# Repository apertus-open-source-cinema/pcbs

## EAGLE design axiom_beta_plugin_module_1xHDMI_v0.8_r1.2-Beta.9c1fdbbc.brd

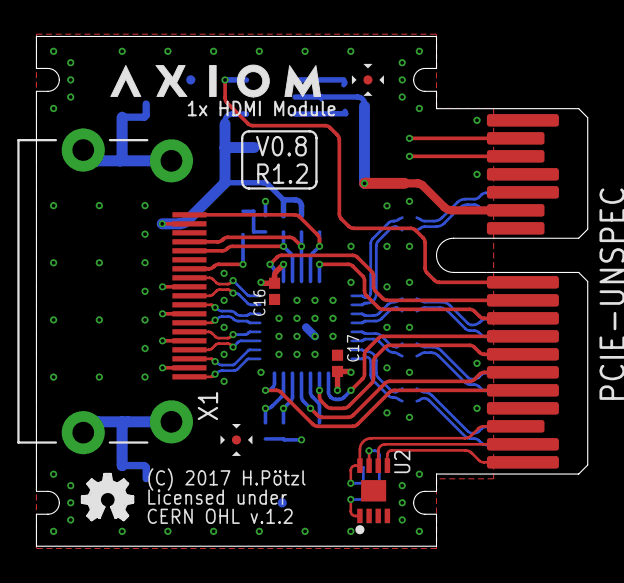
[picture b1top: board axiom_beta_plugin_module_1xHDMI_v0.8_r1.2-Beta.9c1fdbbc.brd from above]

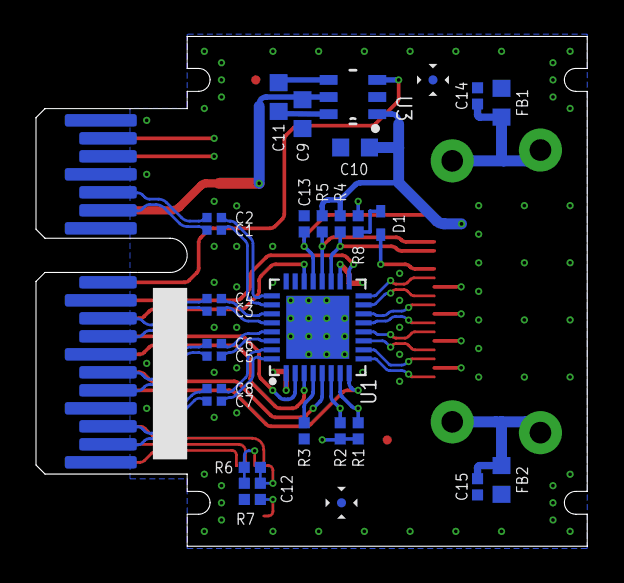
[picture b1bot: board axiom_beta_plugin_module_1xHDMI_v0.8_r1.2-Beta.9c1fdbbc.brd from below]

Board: 4 copper layers, 30.6 x 28.3 mm, 39 parts (30 on the bottom side), 50 nets.

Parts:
C1, C2, C3, C4, C5, C6, C7, C8: 100n; 0402-C
C9: 2u2; 0603-B
C10: 10u; 0603-B
C11: 220n; 0603-B
C12, C16, C17: 100n; 0402-B
C13: 1-10n; 0402-B
C14, C15: 10n; 0402-B
D1: SOD523
F1, F2, F3, F4: FIDUCIAL; FID_ARROW
FB1, FB2: 0603-B
LOGO2: OSHW_LOGO_FILLX0100-NT; OSHW_FILLX100_NOTEXT
PCIE-UNSPEC: PCIE-36-AXIOM
R1, R2, R4, R5: 2k2; 0402-B
R3: 12k4; 0402-B
R6: 10k; 0402-B
R7: 1k; 0402-B
R8: 0402-B
U1: PTN3363; HVQFN32
U2: BR24G04NUX; DFN200X300X100-9N
U3: REG710-DBV; DBV
U$1: AXIOM_LOGO459X70; AXIOM_LOGO_459X70
X1: HDMI-10029449; 10029449-X01XLF

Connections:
3V3: C9.1, C16.1, C17.1, PCIE-UNSPEC.B13, R1.1, R2.1, R8.1, U1.1, U1.18, U3.5
5V0: C10.1, R4.1, R5.1, U3.1, X1.18
!OE!: PCIE-UNSPEC.B10, U1.17
CLOCK_N: U1.16, X1.12
CLOCK_P: U1.15, X1.10
DATA0_N: U1.14, X1.9
DATA0_P: U1.13, X1.7
DATA1_N: U1.12, X1.6
DATA1_P: U1.11, X1.4
DATA2_N: U1.10, X1.3
DATA2_P: U1.9, X1.1
DDC_EN: PCIE-UNSPEC.B9, U1.22
DDET: PCIE-UNSPEC.B7, U1.3
EN: PCIE-UNSPEC.B11, U3.3
EQ0: PCIE-UNSPEC.B5, U1.8
EQ1: PCIE-UNSPEC.B8, U1.2
GND: C9.2, C10.2, C12.2, C13.2, C14.2, C15.2, C16.2, C17.2, FB1.2, FB2.2, PCIE-UNSPEC.A1, PCIE-UNSPEC.A4, PCIE-UNSPEC.A7, PCIE-UNSPEC.A10, PCIE-UNSPEC.A12, PCIE-UNSPEC.A15, PCIE-UNSPEC.A18, PCIE-UNSPEC.B15, PCIE-UNSPEC.B18, R3.2, R7.2, U1.24, U1.EP, U2.1, U2.2, U2.3, U2.4, U2.EP, U3.2, X1.2, X1.5, X1.8, X1.11, X1.17
HDMI_CEC: D1.C, X1.13
HDMI_HP: C13.1, U1.21, X1.19
HDMI_SCL: R4.2, U1.19, X1.15
HDMI_SDA: R5.2, U1.20, X1.16
I2C_V: C12.1, PCIE-UNSPEC.B3, R6.1, U2.8
IHP: PCIE-UNSPEC.B6, U1.5
IN_D1_N: C2.1, U1.25
IN_D1_P: C1.1, U1.26
IN_D2_N: C4.1, U1.27
IN_D2_P: C3.1, U1.28
IN_D3_N: C6.1, U1.29
IN_D3_P: C5.1, U1.30
IN_D4_N: C8.1, U1.31
IN_D4_P: C7.1, U1.32
ISCL: PCIE-UNSPEC.B16, R1.2, U1.7
ISDA: PCIE-UNSPEC.B17, R2.2, U1.6
LVDS_0_N: C8.2, PCIE-UNSPEC.A3
LVDS_0_P: C7.2, PCIE-UNSPEC.A2
LVDS_1_N: C6.2, PCIE-UNSPEC.A6
LVDS_1_P: C5.2, PCIE-UNSPEC.A5
LVDS_2_N: C4.2, PCIE-UNSPEC.A9
LVDS_2_P: C3.2, PCIE-UNSPEC.A8
LVDS_3_N: C2.2, PCIE-UNSPEC.A14
LVDS_3_P: C1.2, PCIE-UNSPEC.A13
unnamed: C11.1, U3.6
unnamed: C11.2, U3.4
unnamed: C14.1, FB1.1, X1.Z1, X1.Z2
unnamed: R6.2, R7.1, U2.7
unnamed: C15.1, FB2.1, X1.Z3, X1.Z4
unnamed: R3.1, U1.4
unnamed: D1.A, R8.2
SCL: PCIE-UNSPEC.B2, U2.6
SDA: PCIE-UNSPEC.B1, U2.5

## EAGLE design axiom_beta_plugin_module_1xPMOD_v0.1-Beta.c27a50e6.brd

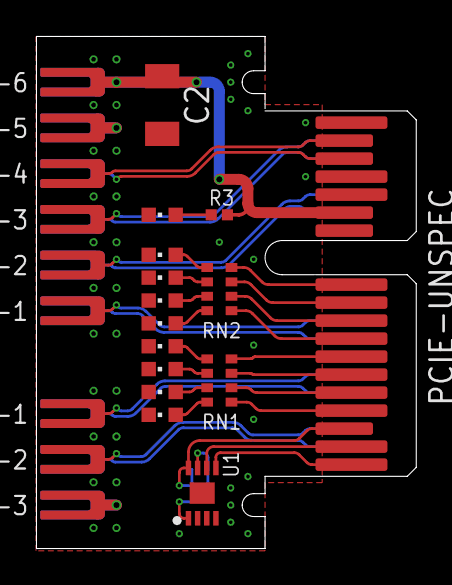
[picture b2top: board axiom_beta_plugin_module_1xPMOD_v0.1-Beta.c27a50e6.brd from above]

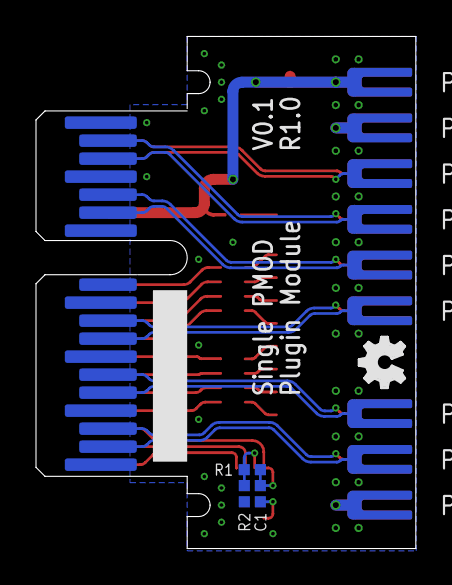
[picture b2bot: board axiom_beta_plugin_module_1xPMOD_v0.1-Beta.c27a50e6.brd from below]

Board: 4 copper layers, 21.1 x 28.4 mm, 38 parts (13 on the bottom side), 35 nets.

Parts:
C1: 100n; 0402-B
C2: 100u; 1206-A
LED0, LED1, LED2, LED3, LED4, LED5, LED6, LED7, LED8: CHIPLED_0603
LOGO1, LOGO2: OSHW_LOGO_FILLX0100-NT; OSHW_FILLX100_NOTEXT
PCIE-UNSPEC: PCIE-36-AXIOM
PMOD1-1, PMOD1-2, PMOD1-3, PMOD1-4, PMOD1-5, PMOD1-6, PMOD1-7, PMOD1-8, PMOD1-9, PMOD1-10, PMOD1-11, PMOD1-12, PMOD2-1, PMOD2-2, PMOD2-3, PMOD2-4, PMOD2-5, PMOD2-6: 1.6X3.8U-MM
R1, R3: 10k; 0402-B
R2: 1k; 0402-B
RN1, RN2: 10k; CAY16
U1: BR24G04NUX; DFN200X300X100-9N

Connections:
GND: C1.2, C2.2, LED0.C, LED1.C, LED2.C, LED3.C, LED4.C, LED5.C, LED6.C, LED7.C, LED8.C, PCIE-UNSPEC.A1, PCIE-UNSPEC.A4, PCIE-UNSPEC.A7, PCIE-UNSPEC.A10, PCIE-UNSPEC.A12, PCIE-UNSPEC.A15, PCIE-UNSPEC.A18, PCIE-UNSPEC.B15, PCIE-UNSPEC.B18, PMOD1-5.1, PMOD1-11.1, PMOD2-3.1, PMOD2-6.1, R2.2, U1.1, U1.2, U1.3, U1.4, U1.EP
I2C_V: C1.1, PCIE-UNSPEC.B3, R1.1, U1.8
IO0: PCIE-UNSPEC.B4, RN1.5
IO1: PCIE-UNSPEC.B5, RN1.6
IO2: PCIE-UNSPEC.B6, RN1.7
IO3: PCIE-UNSPEC.B7, RN1.8
IO4: PCIE-UNSPEC.B8, RN2.5
IO5: PCIE-UNSPEC.B9, RN2.6
IO6: PCIE-UNSPEC.B10, RN2.7
IO7: PCIE-UNSPEC.B11, RN2.8
LVDS_0_N: PCIE-UNSPEC.A3, PMOD2-2.1
LVDS_0_P: PCIE-UNSPEC.A2, PMOD2-5.1
LVDS_1_N: PCIE-UNSPEC.A6, PMOD2-1.1
LVDS_1_P: PCIE-UNSPEC.A5, PMOD2-4.1
LVDS_2_N: PCIE-UNSPEC.A9, PMOD1-1.1
LVDS_2_P: PCIE-UNSPEC.A8, PMOD1-7.1
LVDS_3_N: PCIE-UNSPEC.A14, PMOD1-2.1
LVDS_3_P: PCIE-UNSPEC.A13, PMOD1-8.1
LVDS_4_N: PCIE-UNSPEC.A17, PMOD1-3.1
LVDS_4_P: PCIE-UNSPEC.A16, PMOD1-9.1
LVDS_5_N: PCIE-UNSPEC.B17, PMOD1-4.1
LVDS_5_P: PCIE-UNSPEC.B16, PMOD1-10.1
unnamed: R1.2, R2.1, U1.7
unnamed: LED3.A, RN1.1
unnamed: LED2.A, RN1.2
unnamed: LED1.A, RN1.3
unnamed: LED0.A, RN1.4
unnamed: LED8.A, R3.2
unnamed: LED7.A, RN2.1
unnamed: LED6.A, RN2.2
unnamed: LED5.A, RN2.3
unnamed: LED4.A, RN2.4
PCIE_VCC: C2.1, PCIE-UNSPEC.B13, PMOD1-6.1, PMOD1-12.1, R3.1
SCL: PCIE-UNSPEC.B2, U1.6
SDA: PCIE-UNSPEC.B1, U1.5

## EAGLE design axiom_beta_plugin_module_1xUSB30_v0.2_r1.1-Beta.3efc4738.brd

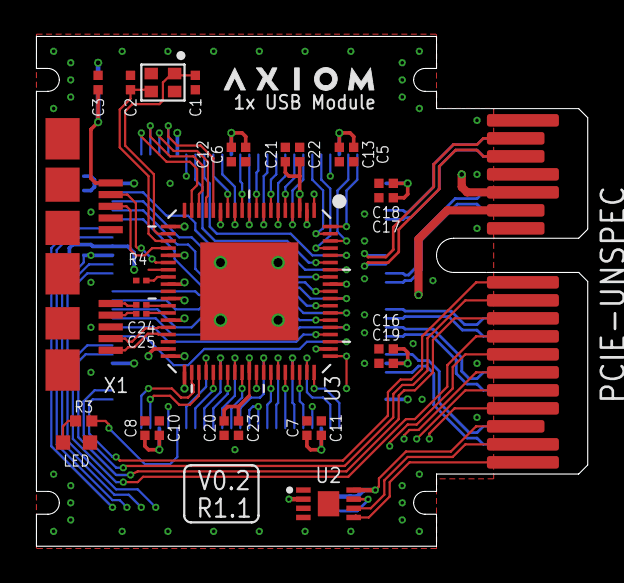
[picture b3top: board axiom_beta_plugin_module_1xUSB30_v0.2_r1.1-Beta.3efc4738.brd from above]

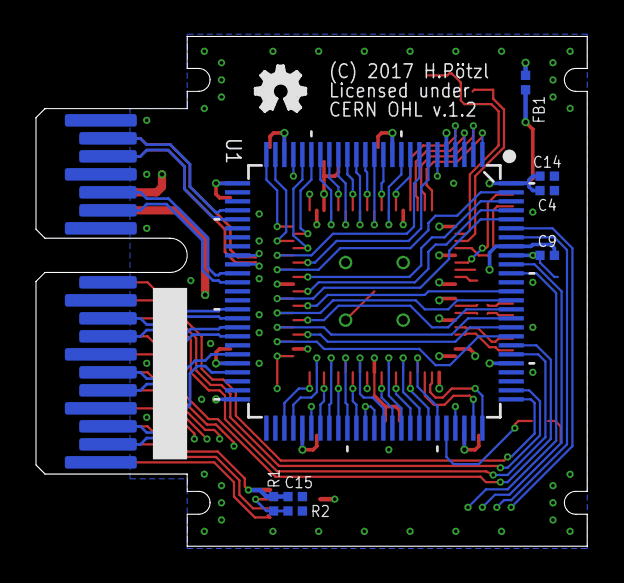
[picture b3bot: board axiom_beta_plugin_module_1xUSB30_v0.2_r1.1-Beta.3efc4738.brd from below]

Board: 4 copper layers, 30.6 x 28.3 mm, 39 parts (9 on the bottom side), 90 nets.

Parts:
C1, C2: 12p; 0402-C
C3, C9, C10, C11, C12, C13, C14, C15, C18, C19, C22, C23: 100n; 0402-C
C4, C5, C6, C7, C8, C16, C17, C20, C21: 4u7; 0402-C
C24, C25: 100n; 0201-C
FB1: 0402-C
LED: LED; CHIPLED_0603
LOGO2: OSHW_LOGO_FILLX0100-NT; OSHW_FILLX100_NOTEXT
PCIE-UNSPEC: PCIE-36-AXIOM
R1: 10k; 0402-C
R2: 1k; 0402-C
R3: 10k; 0402-B
R4: 1k6; 0201-C
U1: MACHXO2-100; MACHXO2-100TQFP
U2: BR24G04NUX; DFN200X300X100-9N
U3: FT601QQFN76; QFN76
U$: AXIOM_LOGO328X50; AXIOM_LOGO_328X50
X1: 10_USB_3.0_2S-SMT; MICRO-B-30-H-SMT
Y1: SMD-4P-2G-2.0X1.6; 2.0X1.6

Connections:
1V0: C20.1, C21.1, C22.1, C23.1, U3.2, U3.3, U3.30, U3.33, U3.39, U3.48
2V5: C16.1, C17.1, C18.1, C19.1, PCIE-UNSPEC.B14, U1.26, U1.46
3V3: C4.1, C5.1, C6.1, C7.1, C8.1, C9.1, C10.1, C11.1, C12.1, C13.1, C14.1, PCIE-UNSPEC.B13, U1.5, U1.11, U1.23, U1.50, U1.55, U1.73, U1.80, U1.93, U1.100, U3.14, U3.20, U3.24, U3.28, U3.38, U3.49, U3.59, U3.68
!OE: U1.9, U3.13
!RD: U1.10, U3.12
!RESET: U1.4, U3.15
!RXF: U1.14, U3.9
!SIWU: U1.13, U3.10
!TXE: U1.15, U3.8
!WAKEUP: U1.3, U3.16
!WR: U1.12, U3.11
BE_0: U1.19, U3.4
BE_1: U1.18, U3.5
BE_2: U1.17, U3.6
BE_3: U1.16, U3.7
CLK: U1.62, U1.63, U3.58
D0: U1.75, U3.40
D1: U1.74, U3.41
D2: U1.70, U3.42
D3: U1.69, U3.43
D4: U1.68, U3.44
D5: U1.67, U3.45
D6: U1.66, U3.46
D7: U1.65, U3.47
D8: U1.64, U3.50
D9: U1.61, U3.51
D10: U1.60, U3.52
D11: U1.59, U3.53
D12: U1.58, U3.54
D13: U1.57, U3.55
D14: U1.54, U3.56
D15: U1.53, U3.57
D16: U1.83, U3.60
D17: U1.84, U3.61
D18: U1.85, U3.62
D19: U1.86, U3.63
D20: U1.87, U3.64
D21: U1.88, U3.65
D22: U1.96, U3.66
D23: U1.97, U3.67
D24: U1.98, U3.69
D25: U1.99, U3.70
D26: U1.7, U3.71
D27: U1.8, U3.72
D28: U1.21, U3.73
D29: U1.24, U3.74
D30: U1.20, U3.75
D31: U1.25, U3.76
DM: U3.25, X1.2
DONE: PCIE-UNSPEC.B11, U1.76
DP: U3.23, X1.3
GND: C1.2, C2.2, C3.2, C4.2, C5.2, C6.2, C7.2, C8.2, C9.2, C10.2, C11.2, C12.2, C13.2, C14.2, C15.2, C16.2, C17.2, C18.2, C19.2, C20.2, C21.2, C22.2, C23.2, LED.C, PCIE-UNSPEC.A1, PCIE-UNSPEC.A4, PCIE-UNSPEC.A7, PCIE-UNSPEC.A10, PCIE-UNSPEC.A12, PCIE-UNSPEC.A15, PCIE-UNSPEC.A18, PCIE-UNSPEC.B15, PCIE-UNSPEC.B18, R2.2, R4.2, U1.6, U1.22, U1.33, U1.44, U1.49, U1.56, U1.72, U1.79, U1.89, U1.92, U2.1, U2.2, U2.3, U2.4, U2.EP, U3.1, U3.26, U3.29, U3.36, U3.77, X1.5, X1.8, X1.S1, X1.S2, X1.Z1, X1.Z2, X1.Z3, X1.Z4, Y1.2, Y1.4
GPIO0: U1.2, U3.17
GPIO1: U1.1, U3.18
I2C_V: C15.1, PCIE-UNSPEC.B3, R1.1, U2.8
INITN: PCIE-UNSPEC.B10, U1.77
JTAGENB: PCIE-UNSPEC.B8, U1.82
LED: R3.1, U1.71
LVDS_0_N: PCIE-UNSPEC.A3, U1.45
LVDS_0_P: PCIE-UNSPEC.A2, U1.47
LVDS_1_N: PCIE-UNSPEC.A6, U1.42
LVDS_1_P: PCIE-UNSPEC.A5, U1.43
LVDS_2_N: PCIE-UNSPEC.A9, U1.40
LVDS_2_P: PCIE-UNSPEC.A8, U1.41
LVDS_3_N: PCIE-UNSPEC.A14, U1.36
LVDS_3_P: PCIE-UNSPEC.A13, U1.37
LVDS_4_N: PCIE-UNSPEC.A17, U1.29
LVDS_4_P: PCIE-UNSPEC.A16, U1.30
LVDS_5_N: PCIE-UNSPEC.B17, U1.34
LVDS_5_P: PCIE-UNSPEC.B16, U1.35
unnamed: LED.A, R3.2
unnamed: R4.1, U3.27
unnamed: R1.2, R2.1, U2.7
PROGRAMN: PCIE-UNSPEC.B9, U1.81
SCL: PCIE-UNSPEC.B2, U2.6
SDA: PCIE-UNSPEC.B1, U2.5
SSRX_N: U3.34, X1.9
SSRX_P: U3.35, X1.10
SSTX_N: C24.1, X1.6
SSTX_P: C25.1, X1.7
TCK: PCIE-UNSPEC.B5, U1.91
TDI: PCIE-UNSPEC.B6, U1.94
TDO: PCIE-UNSPEC.B7, U1.95
TMS: PCIE-UNSPEC.B4, U1.90
TOD_N: C24.2, U3.31
TOD_P: C25.2, U3.32
VBUS: C3.1, FB1.2, X1.1
VBUS': FB1.1, U3.37
XI: C1.1, U3.21, Y1.1
XO: C2.1, U3.22, Y1.3

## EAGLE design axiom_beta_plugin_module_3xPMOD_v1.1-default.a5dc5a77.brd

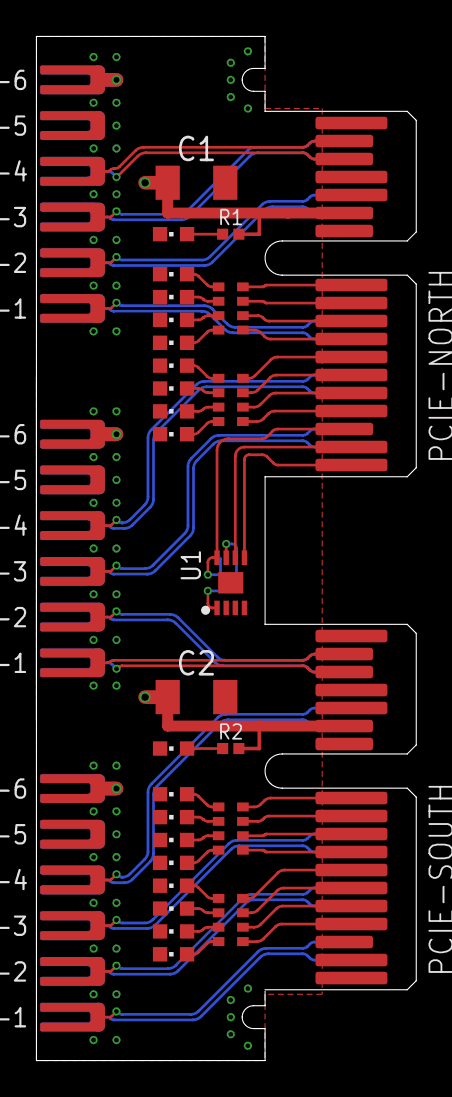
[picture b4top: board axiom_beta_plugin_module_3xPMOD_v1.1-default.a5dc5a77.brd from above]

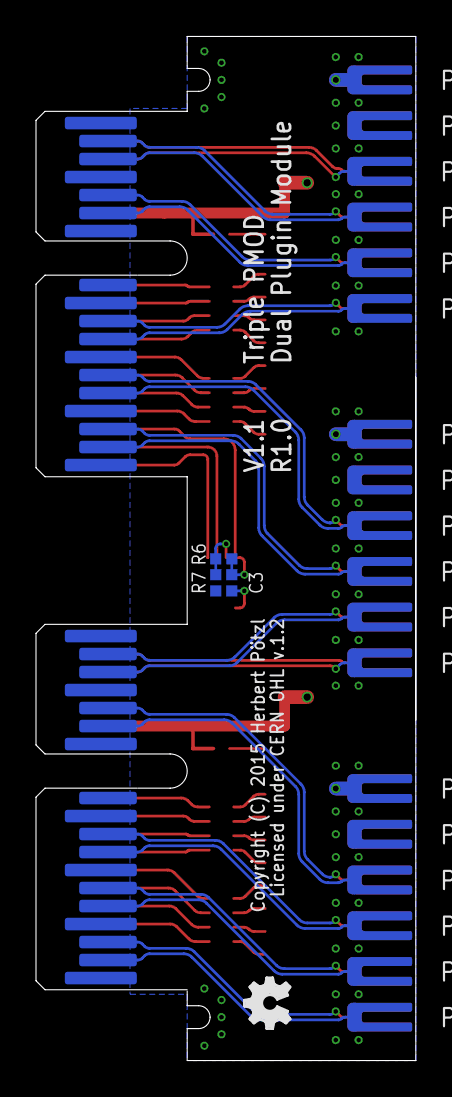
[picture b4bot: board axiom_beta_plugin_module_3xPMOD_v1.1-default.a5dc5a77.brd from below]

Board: 4 copper layers, 21.1 x 56.9 mm, 69 parts (22 on the bottom side), 65 nets.

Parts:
C1, C2: 1206-A
C3: 0402-B
LED0, LED1, LED2, LED3, LED4, LED5, LED6, LED7, LED8, LED9, LED10, LED11, LED12, LED13, LED14, LED15, LED16, LED17: CHIPLED_0603
LOGO1: OSHW_LOGO_FILLX0100-NT; OSHW_FILLX100_NOTEXT
PCIE-NORTH: PCIE-36-AXIOM
PCIE-SOUTH: PCIE-36-AXIOM
PMOD1-1, PMOD1-2, PMOD1-3, PMOD1-4, PMOD1-5, PMOD1-6, PMOD1-7, PMOD1-8, PMOD1-9, PMOD1-10, PMOD1-11, PMOD1-12, PMOD2-1, PMOD2-2, PMOD2-3, PMOD2-4, PMOD2-5, PMOD2-6, PMOD2-7, PMOD2-8, PMOD2-9, PMOD2-10, PMOD2-11, PMOD2-12, PMOD3-1, PMOD3-2, PMOD3-3, PMOD3-4, PMOD3-5, PMOD3-6, PMOD3-7, PMOD3-8, PMOD3-9, PMOD3-10, PMOD3-11, PMOD3-12: 1.6X3.8U-MM
R1, R2, R6, R7: 0402-B
RN1, RN2, RN3, RN4: CAY16
U1: BR24G04NUX; DFN200X300X100-9N

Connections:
GND: C1.2, C2.2, C3.2, LED0.C, LED1.C, LED2.C, LED3.C, LED4.C, LED5.C, LED6.C, LED7.C, LED8.C, LED9.C, LED10.C, LED11.C, LED12.C, LED13.C, LED14.C, LED15.C, LED16.C, LED17.C, PCIE-NORTH.A1, PCIE-NORTH.A4, PCIE-NORTH.A7, PCIE-NORTH.A10, PCIE-NORTH.A12, PCIE-NORTH.A15, PCIE-NORTH.A18, PCIE-NORTH.B15, PCIE-NORTH.B18, PCIE-SOUTH.A1, PCIE-SOUTH.A4, PCIE-SOUTH.A7, PCIE-SOUTH.A10, PCIE-SOUTH.A12, PCIE-SOUTH.A15, PCIE-SOUTH.A18, PCIE-SOUTH.B15, PCIE-SOUTH.B18, PMOD1-5.1, PMOD1-11.1, PMOD2-5.1, PMOD2-11.1, PMOD3-5.1, PMOD3-11.1, R7.2, U1.1, U1.2, U1.3, U1.4, U1.EP
I2C_V: C3.1, PCIE-NORTH.B3, R6.1, U1.8
unnamed: LED3.A, RN1.1
unnamed: LED2.A, RN1.2
unnamed: LED1.A, RN1.3
unnamed: LED0.A, RN1.4
unnamed: LED16.A, R1.2
unnamed: LED17.A, R2.2
unnamed: R6.2, R7.1, U1.7
unnamed: LED7.A, RN2.1
unnamed: LED6.A, RN2.2
unnamed: LED5.A, RN2.3
unnamed: LED4.A, RN2.4
unnamed: LED11.A, RN3.1
unnamed: LED10.A, RN3.2
unnamed: LED9.A, RN3.3
unnamed: LED8.A, RN3.4
unnamed: LED15.A, RN4.1
unnamed: LED14.A, RN4.2
unnamed: LED13.A, RN4.3
unnamed: LED12.A, RN4.4
N_IO0: PCIE-NORTH.B4, RN1.5
N_IO1: PCIE-NORTH.B5, RN1.6
N_IO2: PCIE-NORTH.B6, RN1.7
N_IO3: PCIE-NORTH.B7, RN1.8
N_IO4: PCIE-NORTH.B8, RN2.5
N_IO5: PCIE-NORTH.B9, RN2.6
N_IO6: PCIE-NORTH.B10, RN2.7
N_IO7: PCIE-NORTH.B11, RN2.8
N_LVDS_0_N: PCIE-NORTH.A3, PMOD2-3.1
N_LVDS_0_P: PCIE-NORTH.A2, PMOD2-9.1
N_LVDS_1_N: PCIE-NORTH.A6, PMOD2-4.1
N_LVDS_1_P: PCIE-NORTH.A5, PMOD2-10.1
N_LVDS_2_N: PCIE-NORTH.A9, PMOD1-1.1
N_LVDS_2_P: PCIE-NORTH.A8, PMOD1-7.1
N_LVDS_3_N: PCIE-NORTH.A14, PMOD1-2.1
N_LVDS_3_P: PCIE-NORTH.A13, PMOD1-8.1
N_LVDS_4_N: PCIE-NORTH.A17, PMOD1-3.1
N_LVDS_4_P: PCIE-NORTH.A16, PMOD1-9.1
N_LVDS_5_N: PCIE-NORTH.B17, PMOD1-4.1
N_LVDS_5_P: PCIE-NORTH.B16, PMOD1-10.1
PCIE_N_V: C1.1, PCIE-NORTH.B13, PMOD1-6.1, PMOD1-12.1, PMOD2-6.1, PMOD2-12.1, R1.1
PCIE_S_V: C2.1, PCIE-SOUTH.B13, PMOD3-6.1, PMOD3-12.1, R2.1
SCL: PCIE-NORTH.B2, U1.6
SDA: PCIE-NORTH.B1, U1.5
S_IO0: PCIE-SOUTH.B4, RN3.5
S_IO1: PCIE-SOUTH.B5, RN3.6
S_IO2: PCIE-SOUTH.B6, RN3.7
S_IO3: PCIE-SOUTH.B7, RN3.8
S_IO4: PCIE-SOUTH.B8, RN4.5
S_IO5: PCIE-SOUTH.B9, RN4.6
S_IO6: PCIE-SOUTH.B10, RN4.7
S_IO7: PCIE-SOUTH.B11, RN4.8
S_LVDS_0_N: PCIE-SOUTH.A3, PMOD3-1.1
S_LVDS_0_P: PCIE-SOUTH.A2, PMOD3-7.1
S_LVDS_1_N: PCIE-SOUTH.A6, PMOD3-2.1
S_LVDS_1_P: PCIE-SOUTH.A5, PMOD3-8.1
S_LVDS_2_N: PCIE-SOUTH.A9, PMOD3-3.1
S_LVDS_2_P: PCIE-SOUTH.A8, PMOD3-9.1
S_LVDS_3_N: PCIE-SOUTH.A14, PMOD3-4.1
S_LVDS_3_P: PCIE-SOUTH.A13, PMOD3-10.1
S_LVDS_4_N: PCIE-SOUTH.A17, PMOD2-2.1
S_LVDS_4_P: PCIE-SOUTH.A16, PMOD2-8.1
S_LVDS_5_N: PCIE-SOUTH.B17, PMOD2-1.1
S_LVDS_5_P: PCIE-SOUTH.B16, PMOD2-7.1

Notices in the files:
axiom_beta_plugin_module_1xHDMI_v0.8_r1.2-Beta.9c1fdbbc.brd:
(C) 2017 H.Pötzl
Licensed under
CERN OHL v.1.2
axiom_beta_plugin_module_1xPMOD_v0.1-Beta.c27a50e6.brd:
Copyright (C) 2016 Herbert Pötzl
Licensed under CERN OHL v.1.2
axiom_beta_plugin_module_3xPMOD_v1.1-default.a5dc5a77.brd:
Copyright (C) 2015 Herbert Pötzl
